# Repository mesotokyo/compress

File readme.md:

# MST Compress (Optical Compressor) schematic and PCB for KiCAD

(Japanese version is [here](readme_ja.md) / 日本語版は[こちら](readme_ja.md))

## What is this?

KiCAD files to build PCB of the MST Compress (Optical Compressor). These files are created with KiCad 6.0.

For more information about MST Compress, please check https://meso.tokyo/works/compress .

## Notice

This schematic and PCB file need a `ak_misc` footprint library in [mst-kicad-lib](https://github.com/mesotokyo/mst-kicad-lib). 

## DISCLAIMER

FILES IN THIS REPOSITORY ARE PROVIDED "AS IS", WITHOUT WARRANTY OF ANY KIND, EXPRESS OR IMPLIED, INCLUDING BUT NOT LIMITED TO THE WARRANTIES OF MERCHANTABILITY, FITNESS FOR A PARTICULAR PURPOSE AND NONINFRINGEMENT. IN NO EVENT SHALL THE AUTHORS OR COPYRIGHT HOLDERS BE LIABLE FOR ANY CLAIM, DAMAGES OR OTHER LIABILITY, WHETHER IN AN ACTION OF CONTRACT, TORT OR OTHERWISE, ARISING FROM, OUT OF OR IN CONNECTION WITH IN FILES IN THIS REPOSITORY OR THE USE OR OTHER DEALINGS IN FILES IN THIS REPOSITORY.

## License

CC BY 4.0. For more information, please check https://creativecommons.org/licenses/by/4.0/ .

## Author

MST/mesotokyo

 - https://meso.tokyo/
 - https://x.com/mesotokyox

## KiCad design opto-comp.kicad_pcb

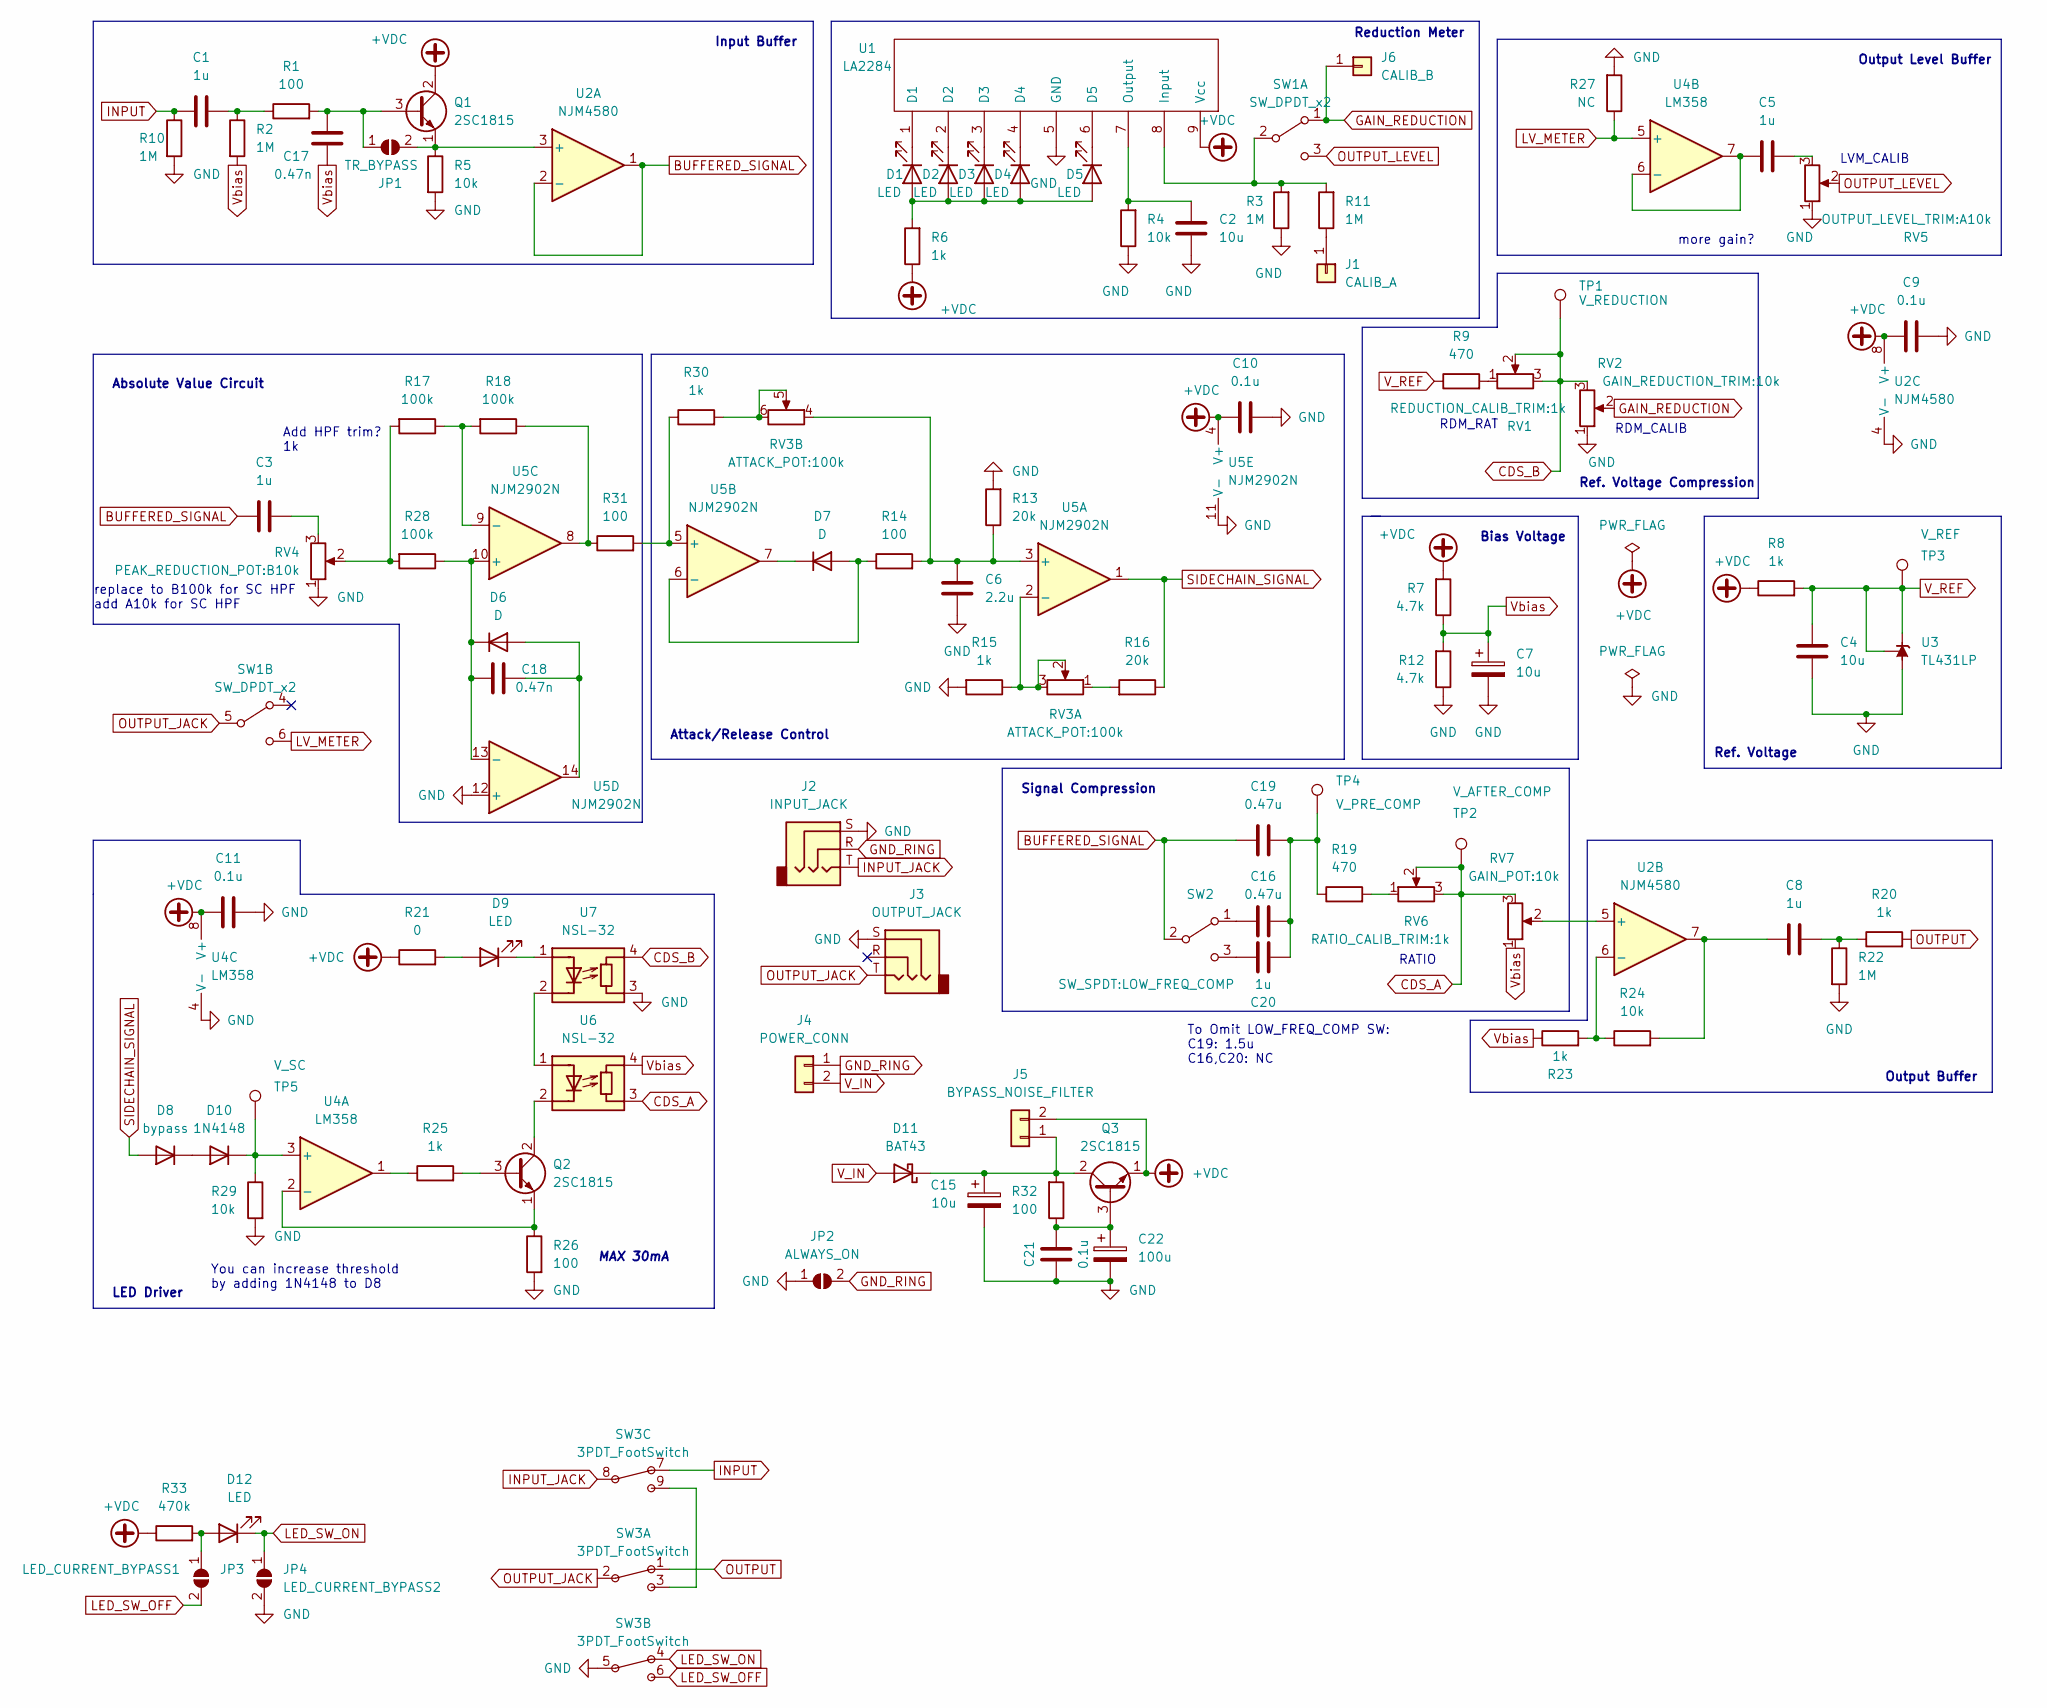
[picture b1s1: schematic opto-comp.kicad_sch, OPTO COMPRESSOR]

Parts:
C1, C3, C8, C20: 1u; C_Rect_L7.0mm_W6.0mm_P5.00mm
C2, C4: 10u; C_Disc_D6.0mm_W2.5mm_P5.00mm
C5: 1u; C_Disc_D3.0mm_W1.6mm_P2.50mm
C6: 2.2u; C_Rect_L7.0mm_W6.0mm_P5.00mm
C7, C15: 10u; CP_Radial_D5.0mm_P2.00mm
C9, C10, C11, C21: 0.1u; C_Disc_D3.0mm_W1.6mm_P2.50mm
C16, C19: 0.47u; C_Rect_L7.0mm_W6.0mm_P5.00mm
C17, C18: 0.47n; C_Disc_D3.0mm_W1.6mm_P2.50mm
C22: 100u; CP_Radial_D5.0mm_P2.00mm
D1, D2, D3, D4, D5, D9, D12: LED; LED_D3.0mm
D6, D7: D; D_DO-35_SOD27_P2.54mm_Vertical_AnodeUp
D8: bypass; D_DO-35_SOD27_P7.62mm_Horizontal
D10: 1N4148; D_DO-35_SOD27_P7.62mm_Horizontal
D11: BAT43; D_DO-35_SOD27_P7.62mm_Horizontal
J1: CALIB_A; PinHeader_1x01_P2.54mm_Vertical
J2: INPUT_JACK; MJ-187
J3: OUTPUT_JACK; MJ-187
J4: POWER_CONN; PinHeader_1x02_P2.54mm_Vertical
J5: BYPASS_NOISE_FILTER; PinHeader_1x02_P2.54mm_Vertical
J6: CALIB_B; PinHeader_1x01_P2.54mm_Vertical
JP1: TR_BYPASS; SolderJumper-2_P1.3mm_Open_RoundedPad1.0x1.5mm
JP2: ALWAYS_ON; SolderJumper-2_P1.3mm_Open_RoundedPad1.0x1.5mm
JP3: LED_CURRENT_BYPASS1; SolderJumper-2_P1.3mm_Open_RoundedPad1.0x1.5mm
JP4: LED_CURRENT_BYPASS2; SolderJumper-2_P1.3mm_Open_RoundedPad1.0x1.5mm
Q1, Q2, Q3: 2SC1815; TO-92_Inline
R1, R14, R26: 100; R_Axial_DIN0204_L3.6mm_D1.6mm_P2.54mm_Vertical
R2, R3, R10, R22: 1M; R_Axial_DIN0204_L3.6mm_D1.6mm_P2.54mm_Vertical
R4, R5, R24, R29: 10k; R_Axial_DIN0204_L3.6mm_D1.6mm_P2.54mm_Vertical
R6, R15, R20, R23, R25, R30: 1k; R_Axial_DIN0204_L3.6mm_D1.6mm_P2.54mm_Vertical
R7, R12: 4.7k; R_Axial_DIN0204_L3.6mm_D1.6mm_P7.62mm_Horizontal
R8: 1k; R_Axial_DIN0204_L3.6mm_D1.6mm_P7.62mm_Horizontal
R9: 470; R_Axial_DIN0204_L3.6mm_D1.6mm_P2.54mm_Vertical
R11: 1M; R_Axial_DIN0204_L3.6mm_D1.6mm_P7.62mm_Horizontal
R13, R16: 20k; R_Axial_DIN0204_L3.6mm_D1.6mm_P2.54mm_Vertical
R17, R18, R28: 100k; R_Axial_DIN0204_L3.6mm_D1.6mm_P2.54mm_Vertical
R19: 470; R_Axial_DIN0204_L3.6mm_D1.6mm_P7.62mm_Horizontal
R21: 0; R_Axial_DIN0204_L3.6mm_D1.6mm_P7.62mm_Horizontal
R27: NC; R_Axial_DIN0204_L3.6mm_D1.6mm_P7.62mm_Horizontal
R31, R32: 100; R_Axial_DIN0204_L3.6mm_D1.6mm_P7.62mm_Horizontal
R33: 470k; R_Axial_DIN0204_L3.6mm_D1.6mm_P2.54mm_Vertical
RV1: REDUCTION_CALIB_TRIM:1k; GF063
RV2: GAIN_REDUCTION_TRIM:10k; GF063
RV3: ATTACK_POT:100k; DualVR_AE-2VR-SW
RV4: PEAK_REDUCTION_POT:B10k; POT-16mm
RV5: OUTPUT_LEVEL_TRIM:A10k; GF063
RV6: RATIO_CALIB_TRIM:1k; GF063
RV7: GAIN_POT:10k; POT-16mm
SW1: SW_DPDT_x2; dpdt-sw-micro
SW2: SW_SPDT:LOW_FREQ_COMP; spdt-sw-micro
SW3: 3PDT_FootSwitch; 3PDT_FootSwitch_ovalpad
TP1: V_REDUCTION; TestPoint_THTPad_D2.0mm_Drill1.0mm
TP2: V_AFTER_COMP; TestPoint_THTPad_D2.0mm_Drill1.0mm
TP3: V_REF; TestPoint_THTPad_D2.0mm_Drill1.0mm
TP4: V_PRE_COMP; TestPoint_THTPad_D2.0mm_Drill1.0mm
TP5: V_SC; TestPoint_THTPad_D2.0mm_Drill1.0mm
U1: LA2284; SIP-9_22.3x3mm_P2.54mm
U2: NJM4580; DIP-8_W7.62mm_Socket
U3: TL431LP; TO-92_Inline
U4: LM358; DIP-8_W7.62mm_Socket
U5: NJM2902N; DIP-14_W7.62mm_Socket
U6, U7: NSL-32; LCR0202

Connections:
+VDC: C9.2, C10.2, C11.2, J5.2, Q1.2 (C), Q3.1 (E), R6.1, R7.2, R8.1, R21.1, R33.1, U1.9 (Vcc), U2.8 (V+), U4.8 (V+), U5.4 (V+)
BUFFERED_SIGNAL: C3.2, C19.2, SW2.2 (B), U2.1, U2.2 (-)
CDS_A: RV6.2, RV6.3, RV7.3, TP2.1, U6.3 (R)
CDS_B: RV1.2, RV1.3, RV2.3, TP1.1, U7.4 (R)
GAIN_REDUCTION: J6.1, RV2.2, SW1.1 (A)
GND: C2.2, C4.2, C6.1, C7.2, C9.1, C10.1, C11.1, C15.2, C21.1, C22.2, J2.S, J3.S, JP2.1 (A), JP4.2 (B), R3.1, R4.1, R5.2, R10.2, R12.1, R13.2, R15.2, R22.2, R26.2, R27.2, R29.2, RV2.1, RV4.1, RV5.1, SW3.5, U1.5 (GND), U2.4 (V-), U3.2 (A), U4.4 (V-), U5.11 (V-), U5.12 (+), U7.3 (R)
GND_RING: J2.R, J4.1, JP2.2 (B)
INPUT: C1.1, R10.1, SW3.7
INPUT_JACK: J2.T, SW3.8
LED_SW_OFF: JP3.2 (B), SW3.6
LED_SW_ON: D12.1 (K), JP4.1 (A), SW3.4
LV_METER: R27.1, SW1.6 (C), U4.5 (+)
unnamed: C1.2, R1.1, R2.1
unnamed: C2.1, R4.2, U1.7 (Output)
unnamed: C3.1, RV4.3
unnamed: C5.1, RV5.3
unnamed: C5.2, U4.6 (-), U4.7
unnamed: C6.2, R13.1, R14.2, RV3.4, U5.3 (+)
unnamed: C8.1, R24.2, U2.7
unnamed: C8.2, R20.1, R22.1
unnamed: C15.1, D11.1 (K), J5.1, Q3.2 (C), R32.2
unnamed: C16.1, C19.1, C20.1, R19.1, TP4.1
unnamed: C16.2, SW2.1 (A)
unnamed: C17.2, JP1.1 (A), Q1.3 (B), R1.2
unnamed: C18.1, D6.2 (A), U5.14
unnamed: C18.2, D6.1 (K), R28.1, U5.10 (+), U5.13 (-)
unnamed: C20.2, SW2.3 (C)
unnamed: C21.2, C22.1, Q3.3 (B), R32.1
unnamed: D1.1 (K), U1.1 (D1)
unnamed: D1.2 (A), D2.2 (A), D3.2 (A), D4.2 (A), D5.2 (A), R6.2
unnamed: D2.1 (K), U1.2 (D2)
unnamed: D3.1 (K), U1.3 (D3)
unnamed: D4.1 (K), U1.4 (D4)
unnamed: D5.1 (K), U1.6 (D5)
unnamed: D7.1 (K), U5.7
unnamed: D7.2 (A), R14.1, U5.6 (-)
unnamed: D9.1 (K), U7.1 (A)
unnamed: D9.2 (A), R21.2
unnamed: D10.1 (K), R29.1, TP5.1, U4.3 (+)
unnamed: D8.1 (K), D10.2 (A)
unnamed: D12.2 (A), JP3.1 (A), R33.2
unnamed: J1.1, R11.1
unnamed: JP1.2 (B), Q1.1 (E), R5.1, U2.3 (+)
unnamed: Q2.1 (E), R26.1, U4.2 (-)
unnamed: Q2.2 (C), U6.2 (K)
unnamed: Q2.3 (B), R25.2
unnamed: R9.2, RV1.1
unnamed: R3.2, R11.2, SW1.2 (B), U1.8 (Input)
unnamed: R15.1, RV3.2, RV3.3, U5.2 (-)
unnamed: R16.2, RV3.1
unnamed: R17.1, R18.2, U5.9 (-)
unnamed: R17.2, R28.2, RV4.2
unnamed: R18.1, R31.1, U5.8
unnamed: R19.2, RV6.1
unnamed: R23.2, R24.1, U2.6 (-)
unnamed: R25.1, U4.1
unnamed: R30.1, R31.2, U5.5 (+)
unnamed: R30.2, RV3.5, RV3.6
unnamed: RV7.2, U2.5 (+)
unnamed: SW3.3, SW3.9
unnamed: U6.1 (A), U7.2 (K)
OUTPUT: R20.2, SW3.1
OUTPUT_JACK: J3.T, SW1.5 (B), SW3.2
OUTPUT_LEVEL: RV5.2, SW1.3 (C)
SIDECHAIN_SIGNAL: D8.2 (A), R16.1, U5.1
V_IN: D11.2 (A), J4.2
V_REF: C4.1, R8.2, R9.1, TP3.1, U3.1 (REF), U3.3 (K)
Vbias: C7.1, C17.1, R2.2, R7.1, R12.2, R23.1, RV7.1, U6.4 (R)

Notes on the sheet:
LVM_CALIB
Signal Compression
Reduction Meter
LED Driver
Ref. Voltage
RATIO
MAX 30mA
RDM_RAT
Bias Voltage
Attack/Release Control
Output Level Buffer
Output Buffer
Absolute Value Circuit
RDM_CALIB
more gain?
You can increase threshold by adding 1N4148 to D8
Ref. Voltage Compression
Add HPF trim? 1k
To Omit LOW_FREQ_COMP SW: C19: 1.5u C16,C20: NC
replace to B100k for SC HPF add A10k for SC HPF
Input Buffer

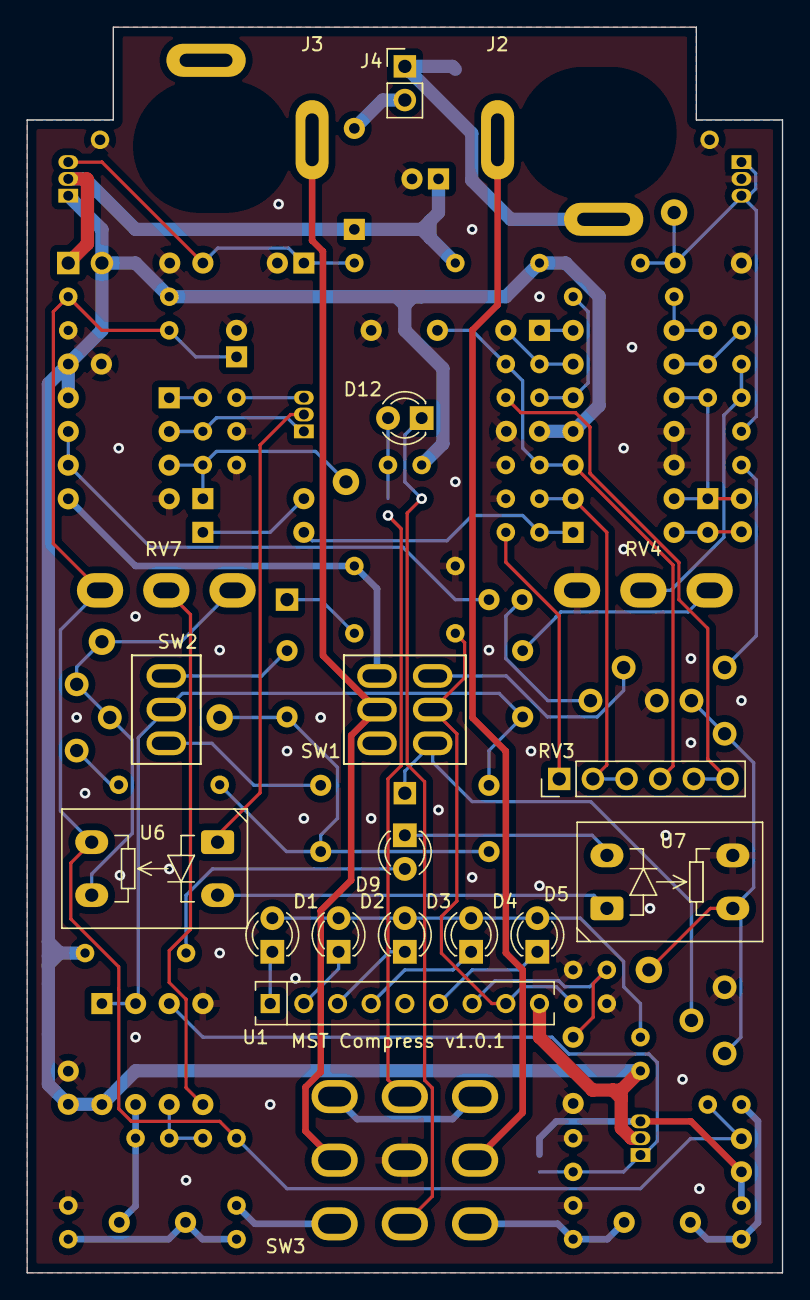
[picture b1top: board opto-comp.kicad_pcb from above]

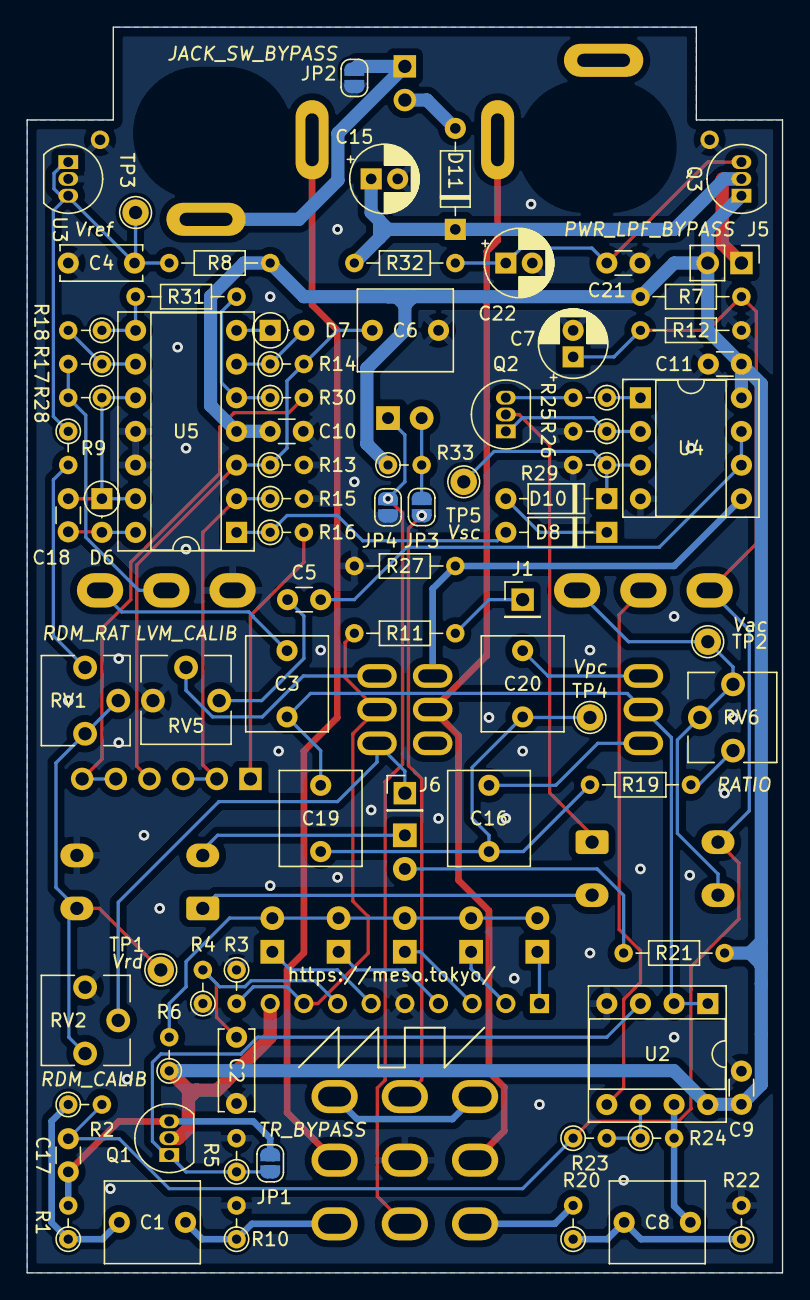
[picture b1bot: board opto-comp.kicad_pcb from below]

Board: 2 copper layers, 57.0 x 94.0 mm, 99 parts (80 on the bottom side), 68 nets.

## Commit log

2024-08-18 fix LCR pattern, add credit
2024-08-18 Replace LM324 to NJM2902N
2024-08-18 fix readme
